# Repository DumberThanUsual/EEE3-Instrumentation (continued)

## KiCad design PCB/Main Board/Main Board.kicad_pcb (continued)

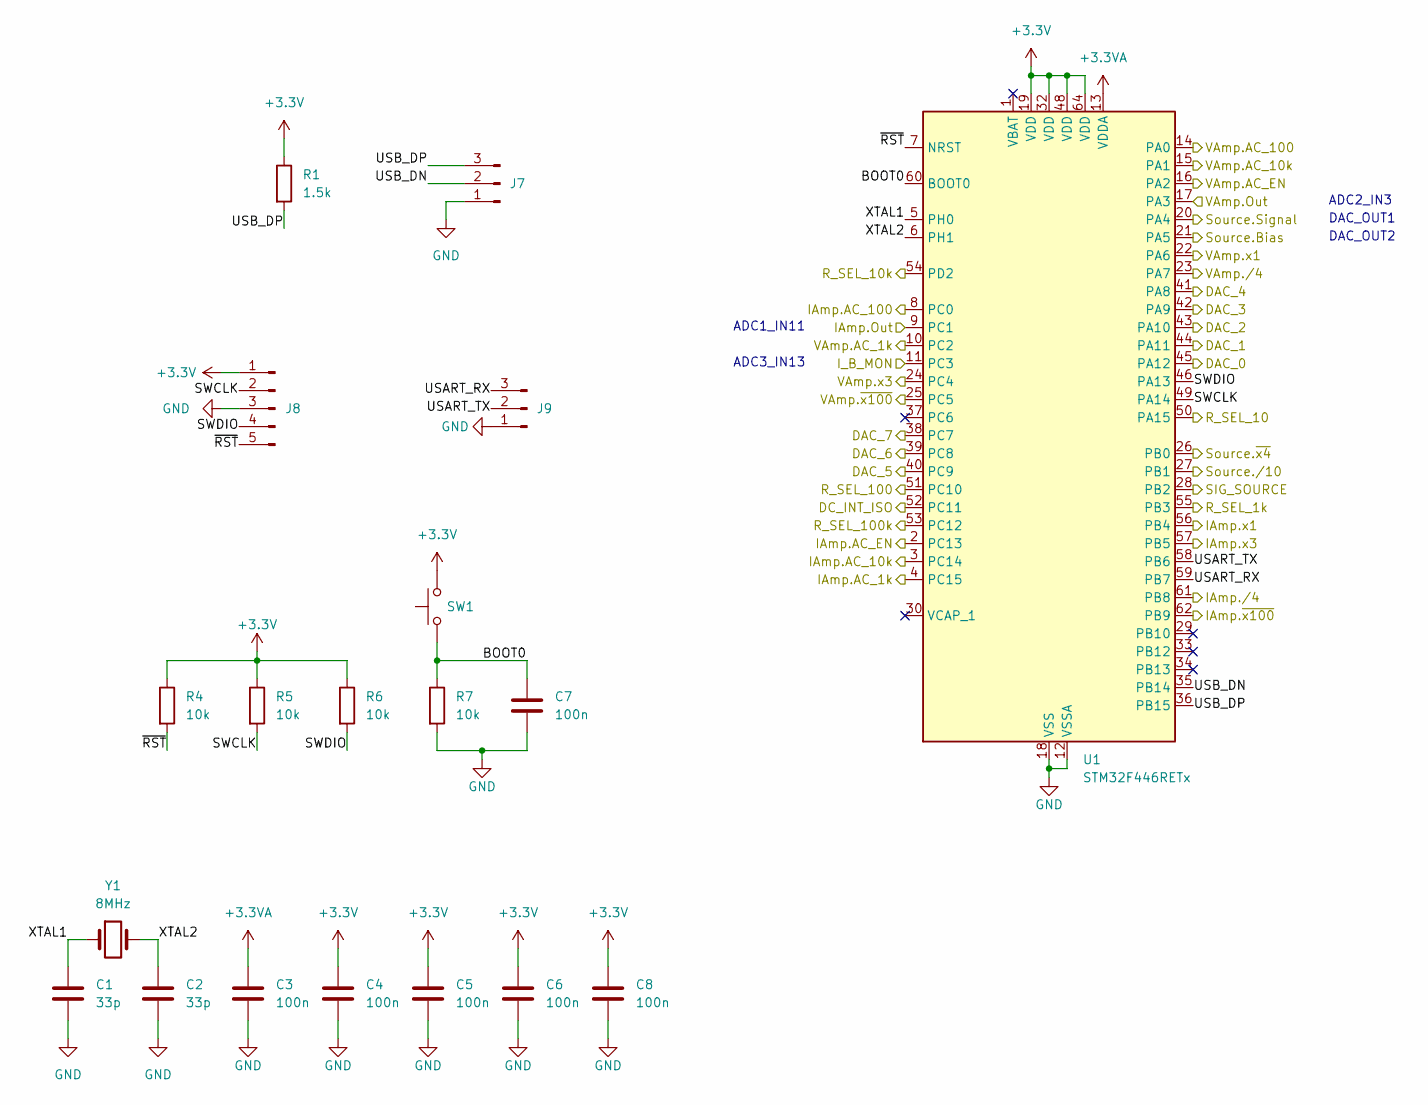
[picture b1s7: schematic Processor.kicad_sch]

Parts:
C1, C2: 33p; C_0805_2012Metric
C3, C4, C5, C6, C7, C8: 100n; C_0805_2012Metric
J7, J9: Conn_01x03_Pin; PinHeader_1x03_P2.54mm_Vertical
J8: Conn_01x05_Pin; PinHeader_1x05_P2.54mm_Vertical
R1: 1.5k; R_0805_2012Metric
R4, R5, R6, R7: 10k; R_0805_2012Metric
SW1: SW_Push; SW_PUSH_6mm
U1: STM32F446RETx; LQFP-64_10x10mm_P0.5mm
Y1: 8MHz; Crystal_SMD_5032-2Pin_5.0x3.2mm

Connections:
+3.3V: C4.1, C5.1, C6.1, C8.1, J8.1, R1.1, R4.1, R5.1, R6.1, SW1.2, U1.19 (VDD), U1.32 (VDD), U1.48 (VDD), U1.64 (VDD); also elsewhere on the board
+3.3VA: C3.1, U1.13 (VDDA); also elsewhere on the board
/Auto-Balancing Bridge/AC_1k: U1.8 (PC0); also elsewhere on the board
/Auto-Balancing Bridge/AC_10k: U1.3 (PC14); also elsewhere on the board
/Auto-Balancing Bridge/AC_100: U1.4 (PC15); also elsewhere on the board
/Auto-Balancing Bridge/AC_EN: U1.2 (PC13); also elsewhere on the board
/Auto-Balancing Bridge/DC_INT_ISO: U1.52 (PC11); also elsewhere on the board
/Auto-Balancing Bridge/I_B_MONITOR: U1.11 (PC3); also elsewhere on the board
/Auto-Balancing Bridge/R_SEL_1k: U1.54 (PD2); also elsewhere on the board
/Auto-Balancing Bridge/R_SEL_10: U1.50 (PA15); also elsewhere on the board
/Auto-Balancing Bridge/R_SEL_10k: U1.55 (PB3); also elsewhere on the board
/Auto-Balancing Bridge/R_SEL_100: U1.51 (PC10); also elsewhere on the board
/Auto-Balancing Bridge/R_SEL_100k: U1.53 (PC12); also elsewhere on the board
/Current Amplifier/Out: U1.9 (PC1); also elsewhere on the board
/Current Amplifier/x1: U1.56 (PB4); also elsewhere on the board
/Current Amplifier/x3: U1.57 (PB5); also elsewhere on the board
/Current Amplifier//4: U1.61 (PB8); also elsewhere on the board
/Current Amplifier/~x100: U1.62 (PB9); also elsewhere on the board
/Processor/BOOT0: C7.1, R7.1, SW1.1, U1.60 (BOOT0)
/Processor/DAC_0: U1.45 (PA12); also elsewhere on the board
/Processor/DAC_1: U1.44 (PA11); also elsewhere on the board
/Processor/DAC_2: U1.43 (PA10); also elsewhere on the board
/Processor/DAC_3: U1.42 (PA9); also elsewhere on the board
/Processor/DAC_4: U1.41 (PA8); also elsewhere on the board
/Processor/DAC_5: U1.40 (PC9); also elsewhere on the board
/Processor/DAC_6: U1.39 (PC8); also elsewhere on the board
/Processor/DAC_7: U1.38 (PC7); also elsewhere on the board
/Processor/SIG_SOURCE: U1.28 (PB2); also elsewhere on the board
/Processor/SWCLK: J8.2, R5.2, U1.49 (PA14)
/Processor/SWDIO: J8.4, R6.2, U1.46 (PA13)
/Processor/Source.Bias: U1.21 (PA5); also elsewhere on the board
/Processor/Source.Signal: U1.20 (PA4); also elsewhere on the board
/Processor/Source./10: U1.27 (PB1); also elsewhere on the board
/Processor/Source.~x4: U1.26 (PB0); also elsewhere on the board
/Processor/USART_RX: J9.3, U1.59 (PB7)
/Processor/USART_TX: J9.2, U1.58 (PB6)
/Processor/USB_DN: J7.2, U1.35 (PB14)
/Processor/USB_DP: J7.3, R1.2, U1.36 (PB15)
/Processor/VAmp.AC_1k: U1.10 (PC2); also elsewhere on the board
/Processor/VAmp.AC_10k: U1.15 (PA1); also elsewhere on the board
/Processor/VAmp.AC_100: U1.14 (PA0); also elsewhere on the board
/Processor/VAmp.AC_EN: U1.16 (PA2); also elsewhere on the board
/Processor/VAmp.Out: U1.17 (PA3); also elsewhere on the board
/Processor/VAmp.x1: U1.22 (PA6); also elsewhere on the board
/Processor/VAmp.x3: U1.24 (PC4); also elsewhere on the board
/Processor/VAmp./4: U1.23 (PA7); also elsewhere on the board
/Processor/VAmp.~x100: U1.25 (PC5); also elsewhere on the board
/Processor/XTAL1: C1.1, U1.5 (PH0), Y1.1
/Processor/XTAL2: C2.1, U1.6 (PH1), Y1.2
/Processor/~RST: J8.5, R4.2, U1.7 (NRST)
GND: C1.2, C2.2, C3.2, C4.2, C5.2, C6.2, C7.2, C8.2, J7.1, J8.3, J9.1, R7.2, U1.12 (VSSA), U1.18 (VSS), U1.31 (VSS), U1.47 (VSS), U1.63 (VSS); also elsewhere on the board

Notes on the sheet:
DAC_OUT1
ADC1_IN11
ADC2_IN3
DAC_OUT2
ADC3_IN13

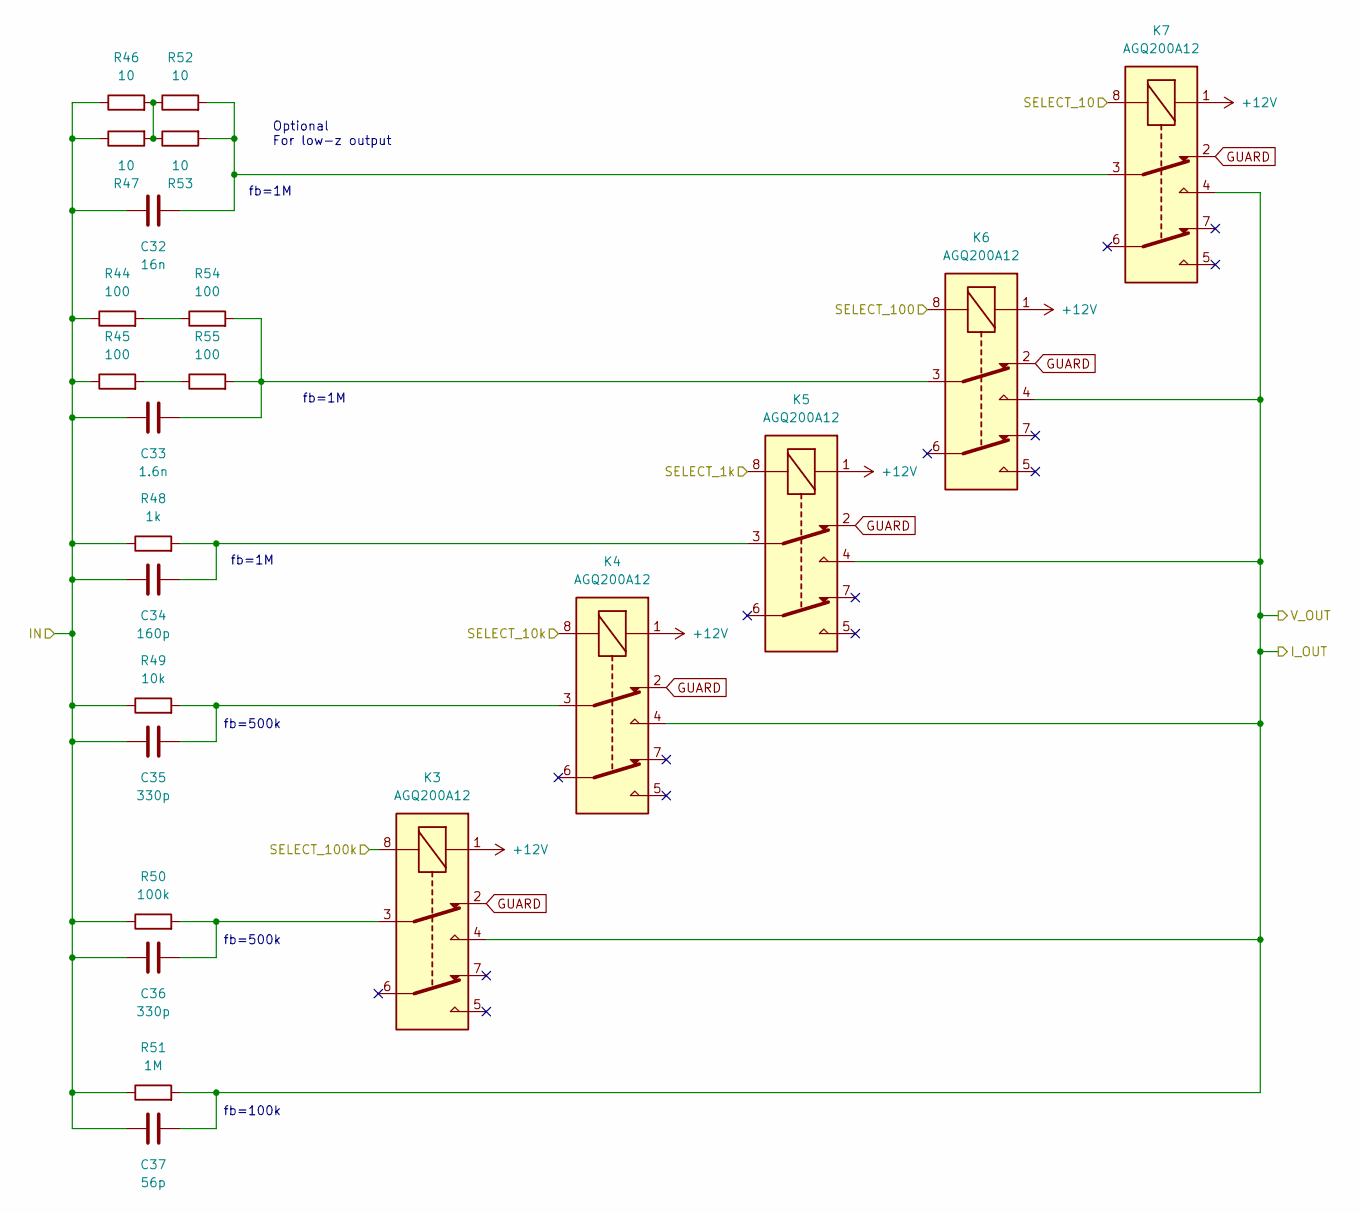
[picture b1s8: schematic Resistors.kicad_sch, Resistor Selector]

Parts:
C32: 16n; C_0805_2012Metric
C33: 1.6n; C_0805_2012Metric
C34: 160p; C_0805_2012Metric
C35, C36: 330p; C_0805_2012Metric
C37: 56p; C_0805_2012Metric
K3, K4, K5, K6, K7: AGQ200A12; RELAY_AGQ_A_PAN; Mouser Part Number 769-AGQ200A12
R44, R45, R54, R55: 100; R_0805_2012Metric
R46, R47, R52, R53: 10; R_2512_6332Metric
R48: 1k; R_0805_2012Metric
R49: 10k; R_0805_2012Metric
R50: 100k; R_0805_2012Metric
R51: 1M; R_0805_2012Metric

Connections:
+12V: K3.1, K4.1, K5.1, K6.1, K7.1; also elsewhere on the board
/Auto-Balancing Bridge/In: C32.1, C33.1, C34.1, C35.1, C36.1, C37.1, R44.1, R45.1, R46.1, R47.1, R48.1, R49.1, R50.1, R51.1; also elsewhere on the board
/Auto-Balancing Bridge/OUT+: C37.2, K3.4, K4.4, K5.4, K6.4, K7.4, R51.2; also elsewhere on the board
/Auto-Balancing Bridge/SEL_1k: K5.8; also elsewhere on the board
/Auto-Balancing Bridge/SEL_10: K7.8; also elsewhere on the board
/Auto-Balancing Bridge/SEL_10k: K4.8; also elsewhere on the board
/Auto-Balancing Bridge/SEL_100: K6.8; also elsewhere on the board
/Auto-Balancing Bridge/SEL_100k: K3.8; also elsewhere on the board
GUARD: K3.2, K4.2, K5.2, K6.2, K7.2; also elsewhere on the board
unnamed: C32.2, K7.3, R52.2, R53.2
unnamed: C33.2, K6.3, R54.2, R55.2
unnamed: C34.2, K5.3, R48.2
unnamed: C35.2, K4.3, R49.2
unnamed: C36.2, K3.3, R50.2
unnamed: R44.2, R54.1
unnamed: R45.2, R55.1
unnamed: R46.2, R47.2, R52.1, R53.1

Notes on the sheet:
fb=100k
fb=500k
fb=1M
Optional For low-z output

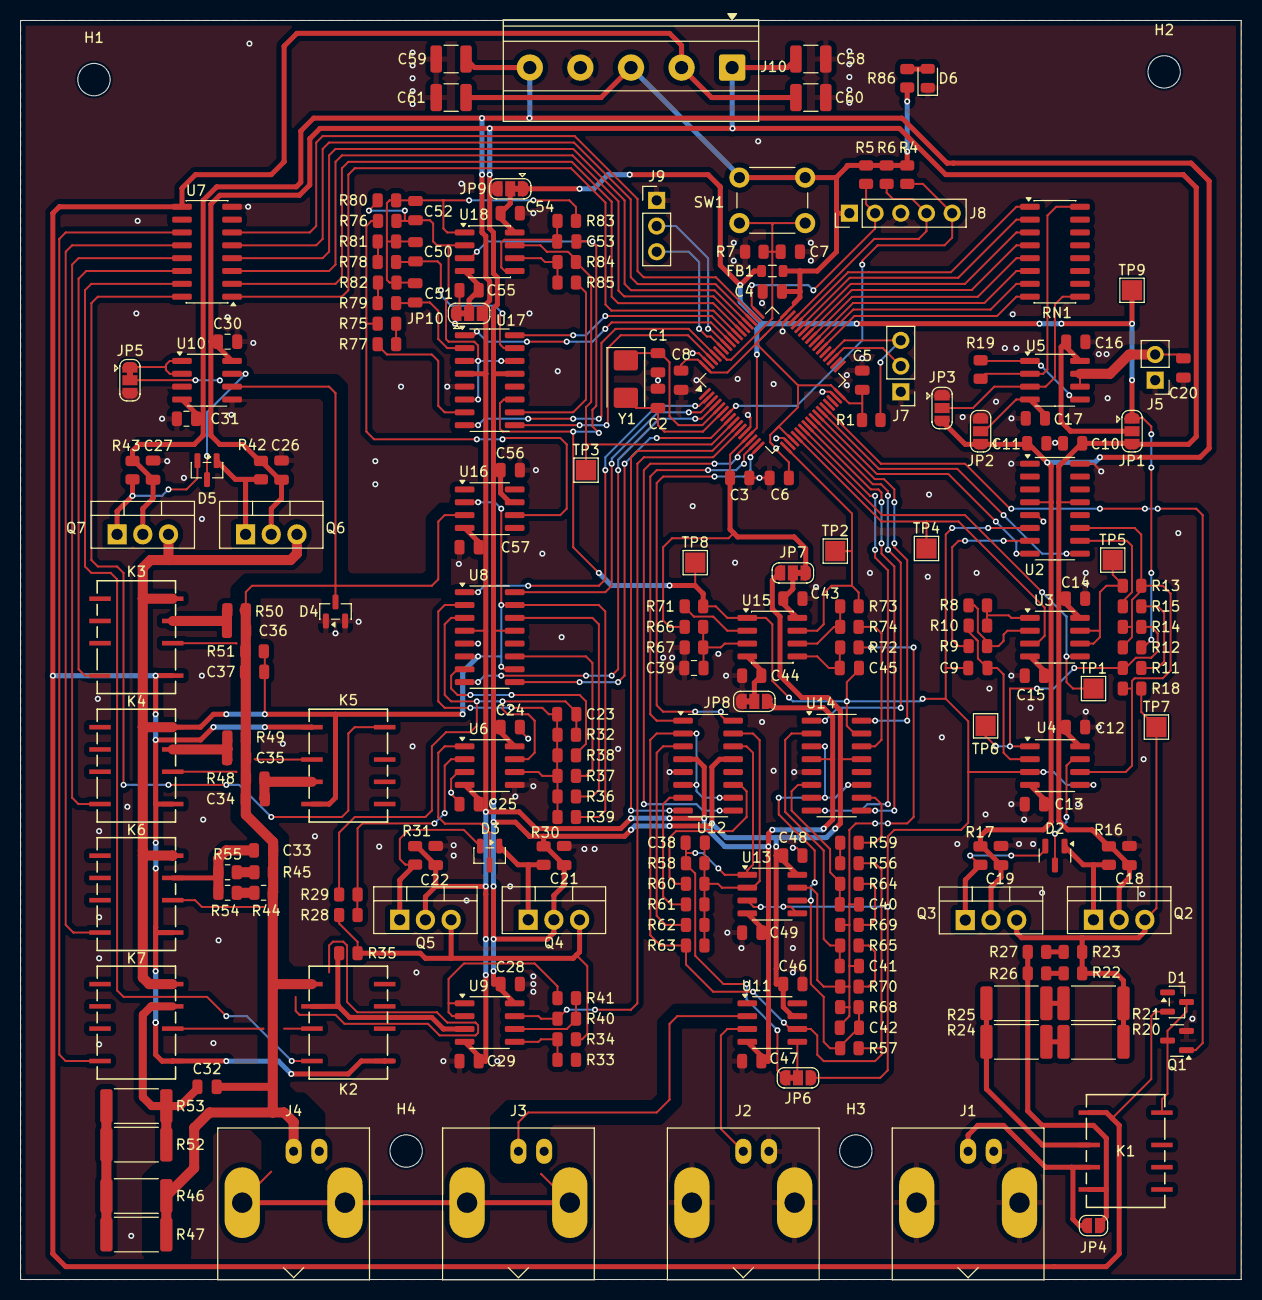
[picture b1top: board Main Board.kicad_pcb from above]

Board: 2 copper layers, 120.7 x 124.5 mm, 219 parts (0 on the bottom side), 156 nets.

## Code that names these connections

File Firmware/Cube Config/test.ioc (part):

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Mcu.Name=STM32F446R(C-E)Tx
Mcu.Package=LQFP64
Mcu.UserName=STM32F446RETx
PA0-WKUP.GPIOParameters=GPIO_Label
PA0-WKUP.GPIO_Label=VAMP_AC100
PA0-WKUP.Signal=GPIO_Output
PA1.GPIOParameters=GPIO_Label
PA1.GPIO_Label=VAMP_AC10K
PA1.Signal=GPIO_Output
PA10.GPIOParameters=GPIO_Label
PA10.GPIO_Label=DAC_2
PA10.Signal=GPIO_Output
PA11.GPIOParameters=GPIO_Label
PA11.GPIO_Label=DAC_1
PA11.Signal=GPIO_Output
PA12.GPIOParameters=GPIO_Label
PA12.GPIO_Label=DAC_0
PA12.Signal=GPIO_Output
PA13.GPIOParameters=GPIO_Label
PA13.GPIO_Label=TMS
PA13.Mode=Serial_Wire
PA13.Signal=SYS_JTMS-SWDIO
PA14.GPIOParameters=GPIO_Label
PA14.GPIO_Label=TCK
PA14.Mode=Serial_Wire
PA14.Signal=SYS_JTCK-SWCLK
PA15.GPIOParameters=GPIO_Label
PA15.GPIO_Label=RANGE_10
PA15.Signal=GPIO_Output
PA2.GPIOParameters=GPIO_Label
PA2.GPIO_Label=VAMP_ACEN
PA2.Signal=GPIO_Output
PA3.GPIOParameters=GPIO_Label
PA3.GPIO_Label=VAMP_OUT
PA3.Signal=ADCx_IN3
PA4.GPIOParameters=GPIO_Label
PA4.GPIO_Label=SOURCE_SIGNAL
PA4.Signal=COMP_DAC1_group
PA5.GPIOParameters=GPIO_Label
PA5.GPIO_Label=SOURCE_BIAS
PA5.Signal=COMP_DAC2_group
PA6.GPIOParameters=GPIO_Label
PA6.GPIO_Label=VAMP_nMUL1
PA6.Signal=GPIO_Output
PA7.GPIOParameters=GPIO_Label
PA7.GPIO_Label=VAMP_DIV4
PA7.Signal=GPIO_Output
PA8.GPIOParameters=GPIO_Label
PA8.GPIO_Label=DAC_4
PA8.Signal=GPIO_Output
PA9.GPIOParameters=GPIO_Label
PA9.GPIO_Label=DAC_3
PA9.Signal=GPIO_Output
PB0.GPIOParameters=GPIO_Label
PB0.GPIO_Label=SOURCE_nMUL4
PB0.Signal=GPIO_Output
PB1.GPIOParameters=GPIO_Label
PB1.GPIO_Label=SOURCE_DIV10
PB1.Signal=GPIO_Output
PB14.Signal=USB_OTG_HS_DM
PB15.Signal=USB_OTG_HS_DP
PB2.GPIOParameters=GPIO_Label
PB2.GPIO_Label=SOURCE_SEL
PB2.Signal=GPIO_Output
PB3.GPIOParameters=GPIO_Label
PB3.GPIO_Label=RANGE_1K
PB3.Signal=GPIO_Output
PB4.GPIOParameters=GPIO_Label
PB4.GPIO_Label=IAMP_nMUL1
PB4.Signal=GPIO_Output
PB5.GPIOParameters=GPIO_Label
PB5.GPIO_Label=IAMP_nMUL3
PB5.Signal=GPIO_Output
PB6.Mode=Asynchronous
PB6.Signal=USART1_TX
PB7.Mode=Asynchronous
PB7.Signal=USART1_RX
PB8.GPIOParameters=GPIO_Label
PB8.GPIO_Label=IAMP_DIV4
PB8.Signal=GPIO_Output
PB9.GPIOParameters=GPIO_Label
PB9.GPIO_Label=IAMP_nMUL100
PB9.Signal=GPIO_Output
PC0.GPIOParameters=GPIO_Label
PC0.GPIO_Label=IAMP_AC100
PC0.Signal=GPIO_Output
PC1.GPIOParameters=GPIO_Label
PC1.GPIO_Label=IAMP_OUT
PC1.Signal=ADCx_IN11
PC10.GPIOParameters=GPIO_Label
PC10.GPIO_Label=RANGE_100
PC10.Signal=GPIO_Output
PC11.GPIOParameters=GPIO_Label
PC11.GPIO_Label=ABB_DC_ISO
PC11.Signal=GPIO_Output
PC12.GPIOParameters=GPIO_Label
PC12.GPIO_Label=RANGE_100K
PC12.Signal=GPIO_Output
PC13.GPIOParameters=GPIO_Label
PC13.GPIO_Label=IAMP_ACEN
PC13.Signal=GPIO_Output
PC14-OSC32_IN.GPIOParameters=GPIO_Label
PC14-OSC32_IN.GPIO_Label=IAMP_AC10K
PC14-OSC32_IN.Signal=GPIO_Output
PC15-OSC32_OUT.GPIOParameters=GPIO_Label
PC15-OSC32_OUT.GPIO_Label=IAMP_AC1K
PC15-OSC32_OUT.Signal=GPIO_Output
PC2.GPIOParameters=GPIO_Label
PC2.GPIO_Label=VAMP_AC1K
PC2.Signal=GPIO_Output
PC3.GPIOParameters=GPIO_Label
PC3.GPIO_Label=IB_MON
PC3.Signal=ADCx_IN13
PC4.GPIOParameters=GPIO_Label
PC4.GPIO_Label=VAMP_nMUL3
PC4.Signal=GPIO_Output
PC5.GPIOParameters=GPIO_Label
PC5.GPIO_Label=VAMP_nMUL100
PC5.Signal=GPIO_Output
PC7.GPIOParameters=GPIO_Label
PC7.GPIO_Label=DAC_7
PC7.Signal=GPIO_Output
PC8.GPIOParameters=GPIO_Label
PC8.GPIO_Label=DAC_6
PC8.Signal=GPIO_Output
PC9.GPIOParameters=GPIO_Label
PC9.GPIO_Label=DAC_5
PC9.Signal=GPIO_Output
PD2.GPIOParameters=GPIO_Label
PD2.GPIO_Label=RANGE_10K
PD2.Signal=GPIO_Output
PH0-OSC_IN.Signal=RCC_OSC_IN
PH1-OSC_OUT.Signal=RCC_OSC_OUT
RCC.HSE_VALUE=8000000
RCC.SYSCLKFreq_VALUE=140000000
RCC.SYSCLKSource=RCC_SYSCLKSOURCE_PLLCLK
board=NUCLEO-F446RE

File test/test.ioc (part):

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Mcu.Name=STM32F446R(C-E)Tx
Mcu.Package=LQFP64
Mcu.UserName=STM32F446RETx
PA0-WKUP.Signal=ADCx_IN0
PA1.Signal=ADCx_IN1
PA13.GPIOParameters=GPIO_Label
PA13.GPIO_Label=TMS
PA13.Mode=Serial_Wire
PA13.Signal=SYS_JTMS-SWDIO
PA14.GPIOParameters=GPIO_Label
PA14.GPIO_Label=TCK
PA14.Mode=Serial_Wire
PA14.Signal=SYS_JTCK-SWCLK
PA15.Signal=S_TIM2_CH1_ETR
PA2.GPIOParameters=GPIO_Label
PA2.GPIO_Label=USART_TX
PA2.Signal=USART2_TX
PA3.GPIOParameters=GPIO_Label
PA3.GPIO_Label=USART_RX
PA3.Signal=USART2_RX
PA4.Signal=COMP_DAC1_group
PA5.GPIOParameters=GPIO_Label
PA5.GPIO_Label=LD2 [Green Led]
PA5.Signal=GPIO_Output
PB3.GPIOParameters=GPIO_Label
PB3.GPIO_Label=SWO
PB3.Signal=SYS_JTDO-SWO
PC13.GPIOParameters=GPIO_Label,GPIO_ModeDefaultEXTI
PC13.GPIO_Label=B1 [Blue PushButton]
PC13.GPIO_ModeDefaultEXTI=GPIO_MODE_IT_FALLING
PC13.Signal=GPXTI13
PC14-OSC32_IN.Signal=RCC_OSC32_IN
PC15-OSC32_OUT.Signal=RCC_OSC32_OUT
PH0-OSC_IN.Signal=RCC_OSC_IN
PH1-OSC_OUT.Signal=RCC_OSC_OUT
RCC.HSE_VALUE=8000000
RCC.SYSCLKFreq_VALUE=140000000
RCC.SYSCLKSource=RCC_SYSCLKSOURCE_PLLCLK
board=NUCLEO-F446RE

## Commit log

2026-01-15 InAmp First Draft
2026-01-15 InAmp Progress
2026-01-16 ABB, InAmp
2026-01-16 Fix schematics location
2026-01-16 Bias sense resistors
2026-01-18 Panik
2026-01-20 Paniking further
2026-01-22 Signal
2026-01-22 parts selection
2026-01-23 minor
2026-01-24 :anguished:
2026-01-24 AAAAAA
2026-01-24 minor: pwr, stm, filters
2026-01-25 :cry:
2026-02-24 code :(
2026-02-24 Reorganise
2026-02-25 power supply
2026-02-25 Code
2026-02-25 buffers designed
2026-02-26 Amplifier Switch
2026-02-26 created buffer subcircuit
2026-02-26 quality of life changes plus wiring plus buffering plus value changes
2026-02-26 footprints and minor
2026-02-26 changed pnp transistor
2026-02-26 footprints and stm wiring
2026-02-26 relays and layout begin
2026-02-26 minor and layout
2026-02-27 amplifer floorplan and relay footprint + minor
2026-02-27 minor and bugfix
2026-02-27 Revert "minor and bugfix"
    This reverts commit 370c3ce365efa92c60832cb4f717ef8263004ca2.
2026-02-27 :ghost:
2026-02-27 fixed
2026-02-27 TO-220
2026-02-27 Layout progress
2026-02-27 transistor tester
2026-02-27 progress
2026-02-27 beep beep
2026-02-27 :-1:
2026-02-28 changed to multiple feedback and minor error correction
2026-02-28 minor schematic changes
2026-02-28 sorry i fell asleep b4 layout
2026-03-01 footprints
2026-03-01 fb capacitances for abb
2026-03-01 checkpoint
2026-03-01 Cryiunbg
2026-03-01 pissing around
2026-03-01 resistor footprints changed
2026-03-01 merge
2026-03-01 co-op test
2026-03-01 YIPEE
2026-03-01 move resistors
2026-03-01 sig source layout prelim
2026-03-01 yipppeee
2026-03-01 relay driver sims
2026-03-01 sig source finished
2026-03-01 hello
2026-03-01 asdfjkhhjk
2026-03-01 Krill me
2026-03-01 phase
2026-03-01 please be nice
2026-03-01 sufferage
2026-03-01 sufferage 2
2026-03-01 layout
2026-03-02 sleepdrunk
2026-03-02 Final Schematic
2026-03-02 cryingggggg
2026-03-02 REEE
2026-03-02 change footprints
2026-03-02 zipped gerbers
2026-03-02 Metal layers
2026-03-02 minor cleanup from the party
2026-03-03 footprints and tps
2026-03-03 bleh
2026-03-04 dsfsdff
2026-03-05 ready to krill myself
2026-03-05 edits
2026-03-05 yeet
2026-03-05 tired
2026-03-05 whats even the point anymore
2026-03-05 slikcreen
2026-03-05 final hopefully
2026-03-05 boop
2026-03-14 matlab app(s)
2026-03-19 minor scpi
2026-03-20 not finished yet
2026-03-21 draw.io
2026-03-22 new schema
2026-03-22 ujpdated code
2026-03-22 xcfdfxgfdfgdsf
2026-03-23 we r cooked
2026-03-23 sims?
2026-03-23 moer sim
2026-03-23 symbols?
2026-03-24 sims 3
2026-03-24 final straws 2
2026-03-24 images
2026-03-24 final sims ❌
